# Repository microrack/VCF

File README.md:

# VCF
Voltage controlled filter for microrack

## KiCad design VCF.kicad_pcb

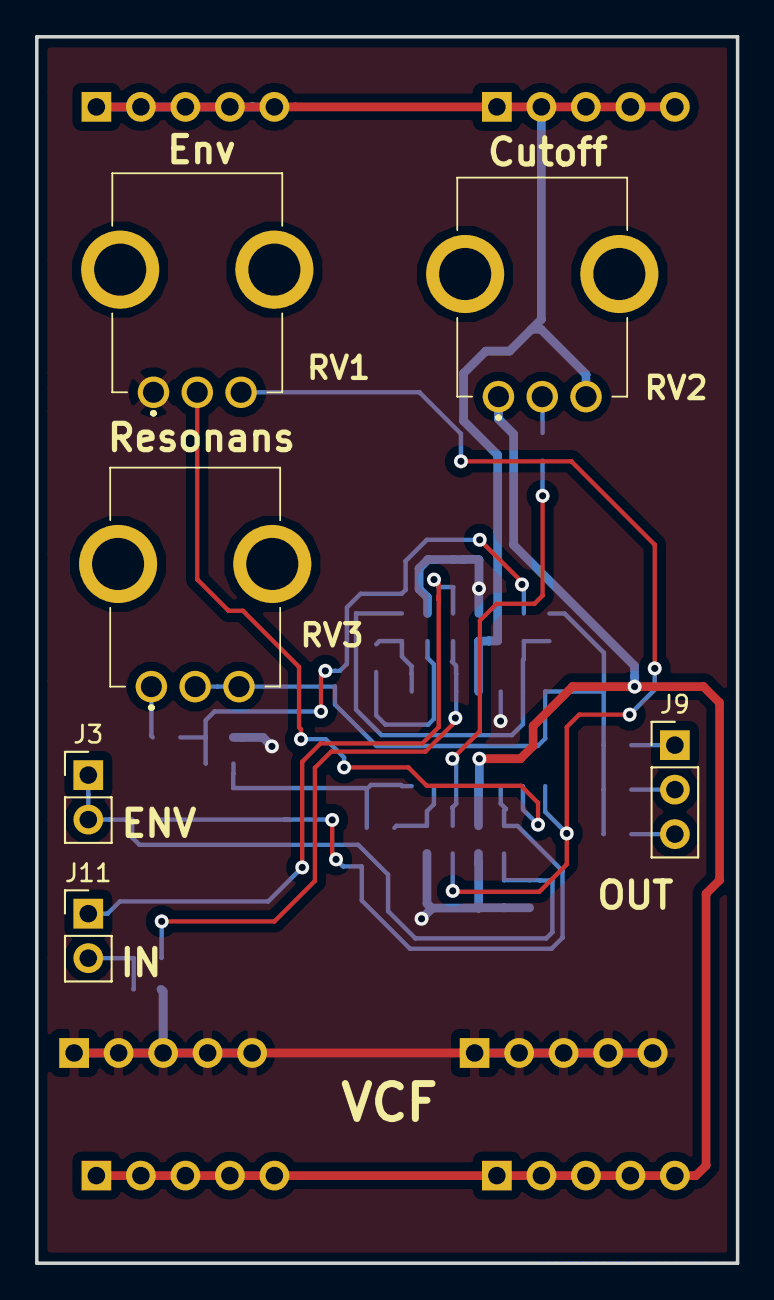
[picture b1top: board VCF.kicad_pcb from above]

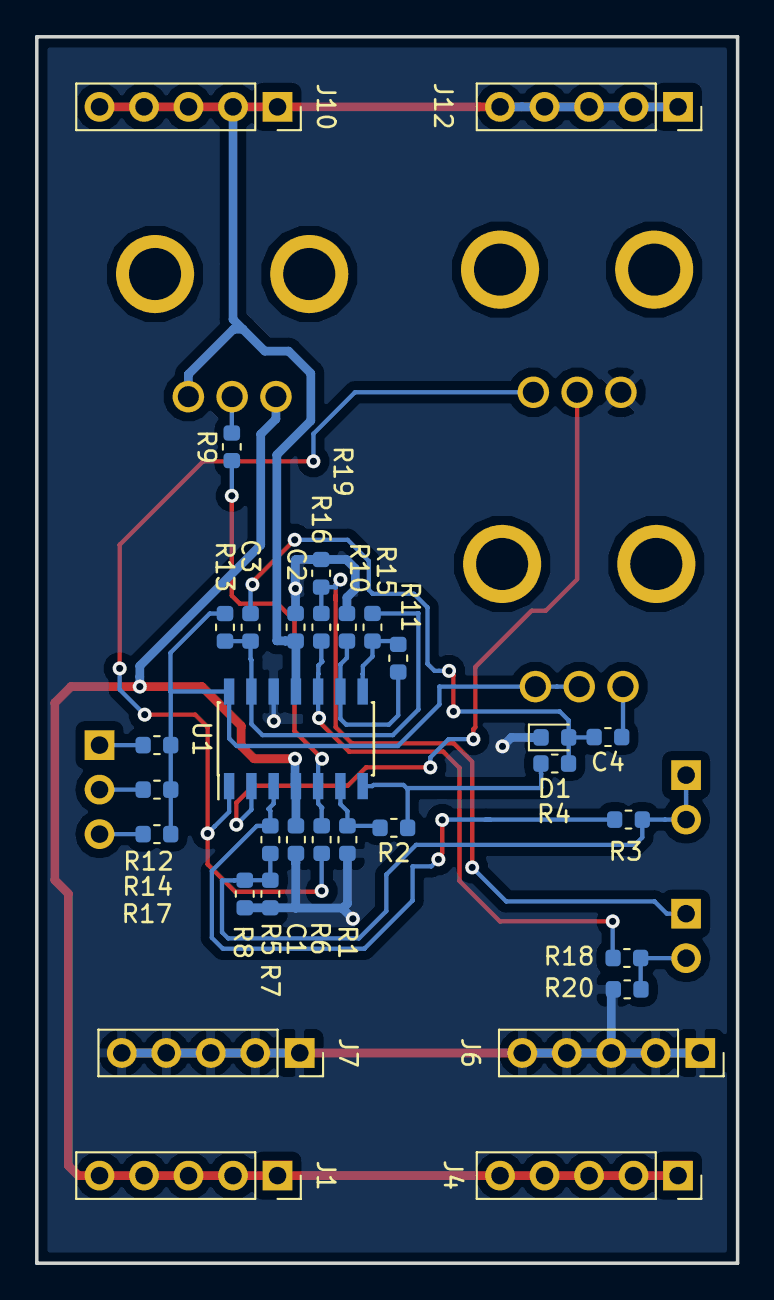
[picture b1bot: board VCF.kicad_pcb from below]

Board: 2 copper layers, 40.0 x 70.0 mm, 38 parts (32 on the bottom side), 23 nets.

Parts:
C1, C2, C3, C4: 0.1 uF; c0603
D1: D; d0603
J1, J4, J6, J7, J10, J12: Conn_01x05_Male; pls1x05
J3: Env; pls1x02
J9: Output; pls1x03
J11: Input; pls1x02
R1, R2, R4, R10, R11: 10K; r0603
R3, R5, R6, R9, R16, R18: 100K; r0603
R7, R8, R19, R20: 1K; r0603
R12, R14, R17: 100R; r0603
R13, R15: 24K; r0603
RV1, RV2, RV3: 10K; R0904N
U1: LM324A; soic-14

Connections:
+5V: C1.2, J1.1, J1.2, J1.3, J1.4, J1.5, J4.1, J4.2, J4.3, J4.4, J4.5, RV2.1, U1.4
-5V: C2.2, J10.1, J10.2, J10.3, J10.4, J10.5, J12.1, J12.2, J12.3, J12.4, J12.5, RV2.3, U1.11
/ENV_2: J3.1, J3.2, R3.2, R5.2, R7.1, R8.1
/IN_2: J11.2, R18.2, R20.1
/OUT_1: J9.1, R12.1
/OUT_2: J9.2, R14.1
GND: C1.1, C2.1, D1.1, J6.1, J6.2, J6.3, J6.4, J6.5, J7.1, J7.2, J7.3, J7.4, J7.5, R1.2, R7.2, R8.2, R10.2, R19.2, R20.2, RV1.1, U1.12
unnamed: C3.1, C4.2, D1.2, R4.1
unnamed: C3.2, R13.2, R15.1, U1.13
unnamed: C4.1, RV3.1
unnamed: J9.3, R17.1
unnamed: J11.1, R16.2, R19.1
unnamed: R1.1, R2.2, U1.6
unnamed: R2.1, R4.2, U1.7
unnamed: R3.1, R5.1, U1.3
unnamed: R6.1, R9.1, U1.5
unnamed: R6.2, RV1.3, U1.1
unnamed: R9.2, RV2.2
unnamed: R10.1, R11.2, U1.9
unnamed: R11.1, R15.2, U1.8
unnamed: R12.2, R13.1, R14.2, R17.2, RV3.2, RV3.3, U1.14
unnamed: R16.1, R18.1, U1.10
unnamed: RV1.2, U1.2

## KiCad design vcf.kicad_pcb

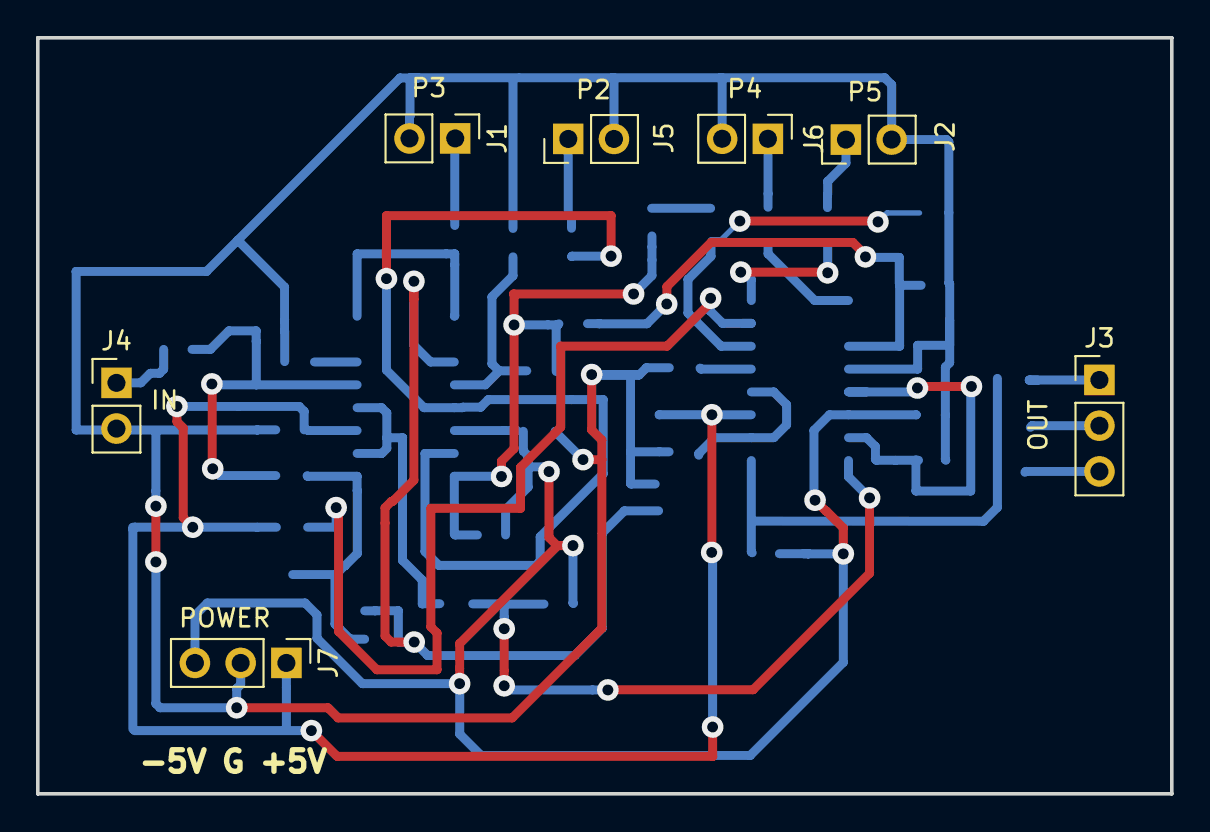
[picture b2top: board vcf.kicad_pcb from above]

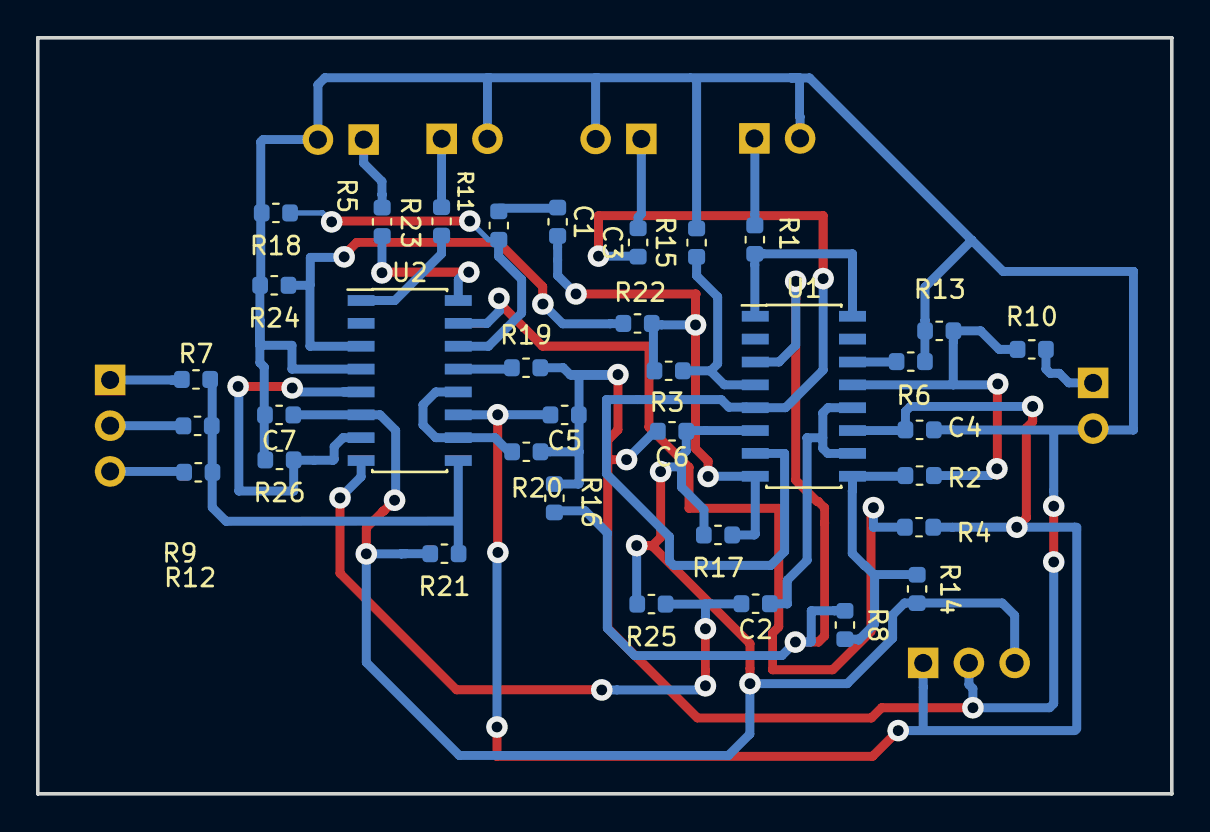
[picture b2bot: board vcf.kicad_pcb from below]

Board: 2 copper layers, 63.0 x 42.0 mm, 42 parts (35 on the bottom side), 31 nets.

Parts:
C1: 4,7uF; c0603
C2: 2000 pF; c0603
C3: 2000pF; c0603
C4, C5, C6, C7: 0.1uF; c0603
J1: P3; pin_1x2V
J2: P5; pin_1x2V
J3: OUT; pin_1x3V
J4: IN; pin_1x2V
J5: P2; pin_1x2V
J6: P4; pin_1x2V
J7: POWER; pin_1x3V
R1, R2, R3, R4, R5, R8, R10, R11, R14, R20, R21, R22, R23, R25, R26: 10K; r0603
R6, R7, R9, R12, R13, R15, R16, R18, R19: 220R; r0603
R17: 1OK; r0603
R24: 1K; r0603
U1, U2: LM13700; SOIC-16

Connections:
+5V: C4.2, C5.2, J7.1, R4.1, U1.11, U2.11
-5V: C6.1, C7.1, J7.3, R14.2, R17.2, R21.2, R25.2, U1.6, U2.6
GND: C4.1, C5.1, C6.2, C7.2, J1.2, J2.2, J4.2, J5.2, J6.2, J7.2, R6.2, R13.2, R15.2, R16.2, R18.2, R19.2, R20.2, R24.2, R26.2, U2.4
unnamed: C1.1, R11.2
unnamed: C1.2, R3.1, R17.1, R22.1, U1.8
unnamed: C2.1, U1.10, U1.12
unnamed: C2.2, R25.1, U2.8
unnamed: C3.1, U1.5, U1.7
unnamed: C3.2, J5.1
unnamed: J1.1, R1.2
unnamed: J2.1, R5.1
unnamed: J3.1, R7.1
unnamed: J3.2, R9.1
unnamed: J3.3, R12.1
unnamed: J4.1, R10.2
unnamed: J6.1, R23.2
unnamed: R1.1, U1.1, U1.16
unnamed: R4.2, U2.15
unnamed: R5.2, U2.16
unnamed: R6.1, U1.14
unnamed: R2.2, R10.1, R13.1, U1.13
unnamed: R11.1, R18.1, U2.14
unnamed: R7.2, R9.2, R12.2, R21.1, U2.9
unnamed: R2.1, R8.2, R14.1, U1.9
unnamed: R3.2, R15.1, U1.4
unnamed: R8.1, R16.1, U1.3
unnamed: R19.1, U2.13
unnamed: R20.1, U2.10, U2.12
unnamed: R22.2, R24.1, U2.3
unnamed: R23.1, U2.1
unnamed: R26.1, U2.5, U2.7

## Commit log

2019-03-31 add kicad project
2019-03-31 add simulation files
2019-03-31 add old simple vcf models/3
2019-03-31 move to simulation dir
2019-04-05 experimental schematic
2019-04-05 Дабаленны библионеки использующиеся в модуле VCF Дабавленны три варианта печатной платы основонных на компонентах типоразмера 1206.
2019-04-05 Библтотеки проекта перенесенны в общую библиотеку. Добавленна плата с толщиной дорожек 0,5 мм и типоразмеровм пасивных элементов 0603. Исправленны пути к библиотекам
2019-04-05 Изменены УГО резисторов с европейского обозначения на Российское Bcghfdktyys genb r ,b,kbjntrfv
2019-04-10 Изменена плата под компоненты 0603
2019-04-10 Плата 40х70 мм. Добавленны подписи компонентов и регуляторов Косметические изменения в схеме, уменьшенно количество разъемов питания
